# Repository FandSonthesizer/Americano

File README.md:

# Americano

A very cool blend of a fuzz and an octave effect.

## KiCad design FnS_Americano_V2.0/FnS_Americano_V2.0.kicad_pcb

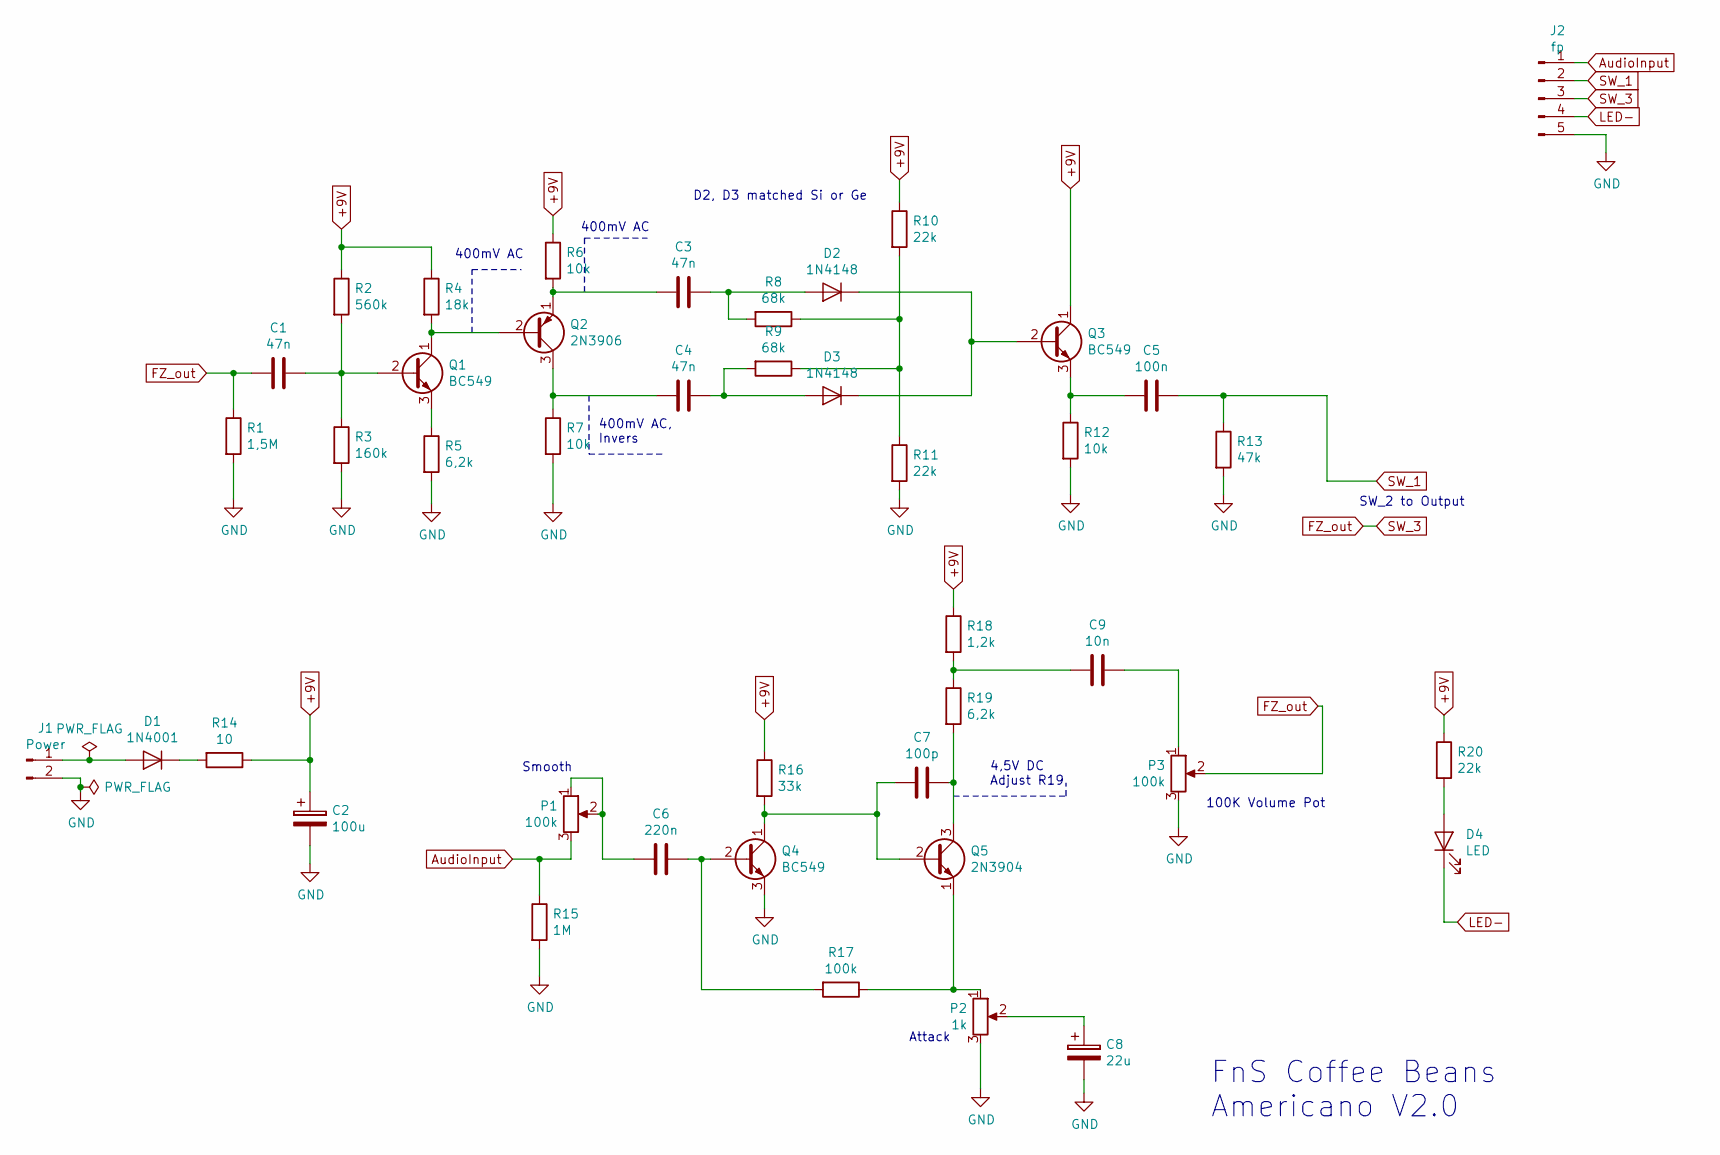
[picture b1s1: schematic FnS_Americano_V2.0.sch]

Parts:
C1, C3, C4: 47n; Kondensator_Keramik
C2: 100u; Elko_D6.3mm_P2.50mm
C5: 100n; Kondensator_Keramik
C6: 220n; Kondensator_Keramik
C7: 100p; Kondensator_Keramik
C8: 22u; Elko_D6.3mm_P2.50mm
C9: 10n; Kondensator_Keramik
D1: 1N4001; Diode_Horizontal
D2, D3: 1N4148; Diode_Horizontal
D4: LED; LED_Vertikal
J1: Power; Stift_x02
J2: fp; PinHeader_1x05_P2.54mm_Vertical
P1, P3: 100k; Potentiometer_Alps_RK09K_Single_Vertical
P2: 1k; Potentiometer_Piher_T-16L_Single_Vertical_Hole
Q1, Q3, Q4: BC549; TO-92_Wide_NIK
Q2: 2N3906; TO-92_Wide_NIK
Q5: 2N3904; TO-92_Wide_NIK
R1: 1,5M; Widerstand_liegend
R2: 560k; Widerstand_liegend
R3: 160k; Widerstand_liegend
R4: 18k; Widerstand_liegend
R5, R19: 6,2k; Widerstand_liegend
R6, R7, R12: 10k; Widerstand_liegend
R8, R9: 68k; Widerstand_liegend
R10, R11, R20: 22k; Widerstand_liegend
R13: 47k; Widerstand_liegend
R14: 10; Widerstand_liegend
R15: 1M; Widerstand_liegend
R16: 33k; Widerstand_liegend
R17: 100k; Widerstand_liegend
R18: 1,2k; Widerstand_liegend

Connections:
+9V: C2.1, Q3.1 (C), R2.1, R4.1, R6.1, R10.1, R14.1, R16.1, R18.1, R20.1
AudioInput: J2.1, P1.3, R15.1
FZ_out: C1.2, J2.3, P3.2, R1.1
GND: C2.2, C8.2, J1.2, J2.5, P2.3, P3.3, Q4.3 (E), R1.2, R3.2, R5.2, R7.2, R11.2, R12.2, R13.2, R15.2
LED-: D4.1 (K), J2.4
unnamed: C1.1, Q1.2 (B), R2.2, R3.1
unnamed: C3.1, D2.2 (A), R8.2
unnamed: C3.2, Q2.1 (E), R6.2
unnamed: C4.1, D3.2 (A), R9.2
unnamed: C4.2, Q2.3 (C), R7.1
unnamed: C5.2, Q3.3 (E), R12.1
unnamed: C6.1, Q4.2 (B), R17.2
unnamed: C6.2, P1.1, P1.2
unnamed: C7.1, Q5.3 (C), R19.2
unnamed: C7.2, Q4.1 (C), Q5.2 (B), R16.2
unnamed: C8.1, P2.2
unnamed: C9.1, P3.1
unnamed: C9.2, R18.2, R19.1
unnamed: D1.1 (K), R14.2
unnamed: D1.2 (A), J1.1
unnamed: D2.1 (K), D3.1 (K), Q3.2 (B)
unnamed: D4.2 (A), R20.2
unnamed: P2.1, Q5.1 (E), R17.1
unnamed: Q1.1 (C), Q2.2 (B), R4.2
unnamed: Q1.3 (E), R5.1
unnamed: R8.1, R9.1, R10.2, R11.1
SW_1: C5.1, J2.2, R13.1

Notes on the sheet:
D2, D3 matched Si or Ge
FnS Coffee Beans Americano V2.0
400mV AC
400mV AC, Invers
100K Volume Pot
4,5V DC Adjust R19
Attack
SW_2 to Output
Smooth

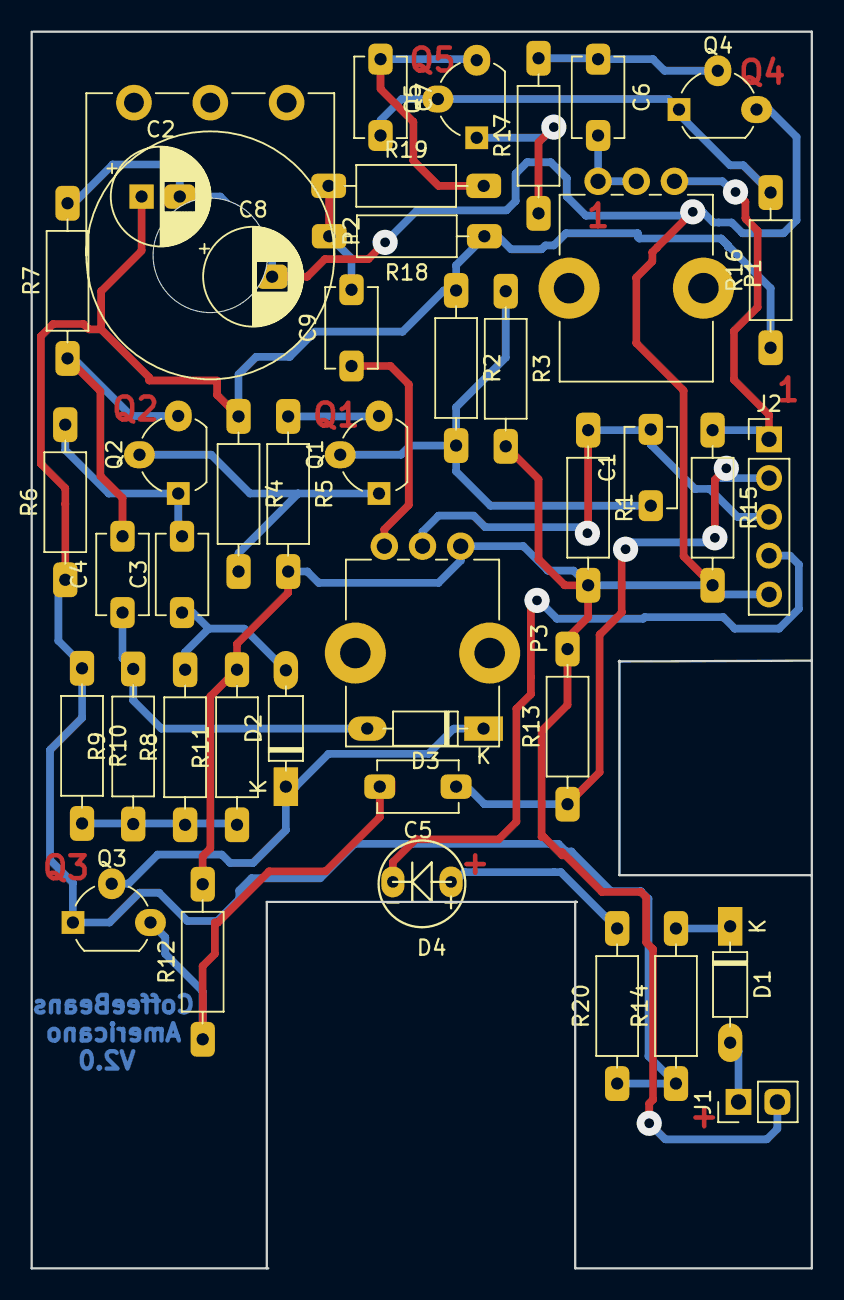
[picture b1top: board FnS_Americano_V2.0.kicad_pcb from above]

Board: 2 copper layers, 51.1 x 81.0 mm, 43 parts (0 on the bottom side), 27 nets.

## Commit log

2020-11-07 Add files via upload
    Add custom kicad libraries
